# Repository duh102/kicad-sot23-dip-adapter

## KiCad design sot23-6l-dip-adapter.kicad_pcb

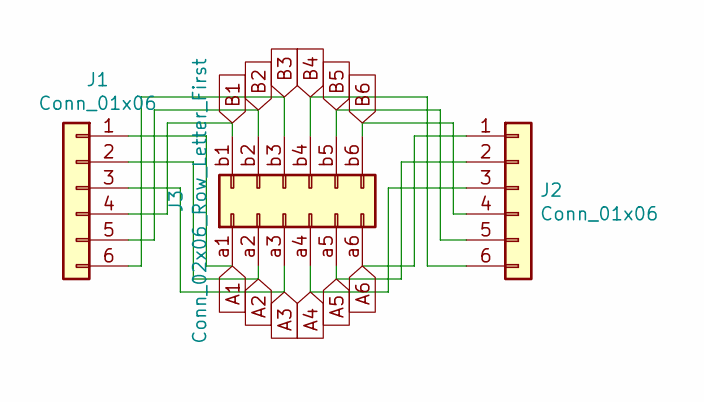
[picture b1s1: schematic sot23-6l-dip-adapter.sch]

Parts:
J1, J2: Conn_01x06; PinHeader_1x06_P2.54mm_Vertical
J3: Conn_02x06_Row_Letter_First; SOT_Socket-6L-CHR-051-2317-060

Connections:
A1: J1.1, J3.a1
A2: J1.2, J3.a2
A3: J1.3, J3.a3
A4: J2.3, J3.a4
A5: J2.2, J3.a5
A6: J2.1, J3.a6
B1: J1.4, J3.b1
B2: J1.5, J3.b2
B3: J1.6, J3.b3
B4: J2.6, J3.b4
B5: J2.5, J3.b5
B6: J2.4, J3.b6

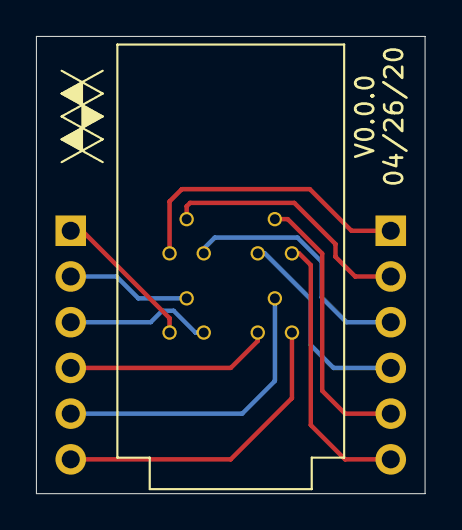
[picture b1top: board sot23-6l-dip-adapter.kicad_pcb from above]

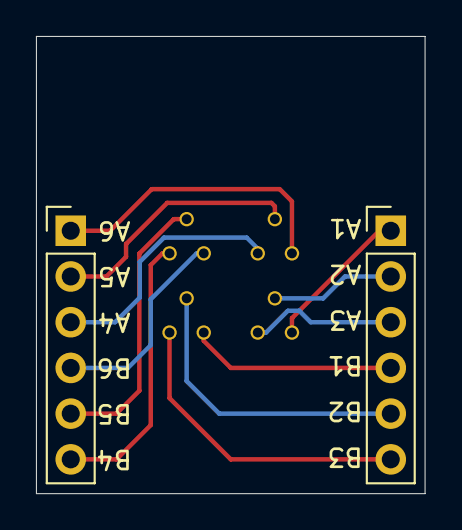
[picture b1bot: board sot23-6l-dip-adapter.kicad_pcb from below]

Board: 2 copper layers, 21.6 x 25.4 mm, 3 parts (2 on the bottom side), 12 nets.
